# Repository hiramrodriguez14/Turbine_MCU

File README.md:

# Horizontal Axis Wind Turbine Electronic Control Unit (ECU)

## Turbine MCU PCB

Printed Circuit Board (PCB) design for the **Turbine Microcontroller Unit (MCU)** of the **Horizontal Axis Wind Turbine Electronic Control Unit (ECU)**.

This repository contains the complete KiCad hardware design, manufacturing files, and production documentation for the embedded controller responsible for turbine monitoring, blade pitch control, sensor acquisition, and communication with the Load Control & User Interface MCU.

---

# Documentation & Demo

| Resource | Link |
| ------------------------ | ------------------------------- |
| 🎥 Project Demonstration | https://www.youtube.com/watch?v=vS5Ok38P1Jk |
| 📄 Final Project Report | https://drive.google.com/file/d/1cckKhvj7mvzCEbm3IqWp0KvrUp9g6mgg/view?usp=sharing |
| 📚 Technical Appendix | https://drive.google.com/file/d/1xu7MtcffDlpna8_BUkwEc_BfjpQJpUep/view?usp=sharing |

---

# Overview

The Turbine MCU PCB serves as the dedicated embedded controller for the mechanical subsystem of the Horizontal Axis Wind Turbine Electronic Control Unit (ECU).

Designed using **KiCad**, this board interfaces directly with the turbine sensors and pitch actuation system, executing all real-time control tasks required for safe turbine operation. It operates alongside the Load Control & User Interface PCB, forming a distributed dual-MCU embedded architecture.

The PCB was designed with reliability, debugging, and manufacturability in mind, incorporating dedicated test points, modular circuitry, and production-ready manufacturing files.

---

# Engineering Highlights

- Custom 2-layer PCB
- Designed in KiCad
- Texas Instruments MSPM0G3507
- Dual servo motor interface
- Hall-effect sensor interface
- Hot-wire anemometer interface
- UART communication
- PWM generation
- Programming and debug header
- Dedicated test points
- Production-ready Gerber files
- Manufacturing BOM
- Pick-and-Place (CPL) files

---

# Hardware Features

The Turbine MCU PCB integrates the following subsystems.

### Turbine Monitoring

- Rotor RPM sensing
- Wind speed acquisition
- Sensor signal conditioning

### Pitch Control

- Dual servo motor outputs
- PWM control interface
- Blade pitch actuation

### Communication

- UART interface with the Load Control & UI MCU
- Programming and debugging interface

### System Management

- Local power regulation
- Test points
- Status indicators

---

# Hardware Architecture

The Turbine MCU PCB serves as the dedicated controller for the turbine's mechanical subsystem.

Primary responsibilities include:

- Wind speed acquisition
- Rotor speed measurement
- Blade pitch control
- Turbine state supervision
- Safety monitoring
- Communication with the Load Control & UI MCU

<p align="center">
<b>Figure 1.</b> Turbine MCU Architecture
</p>

---

# PCB Design

The PCB was developed using KiCad following standard embedded hardware design practices.

Special consideration was given to:

- Servo routing
- Sensor integrity
- Ground plane implementation
- Test point accessibility
- Programming interface accessibility
- Manufacturing compatibility

## Top Layer

<p align="center">
<b>Figure 2.</b> Top Layer PCB Layout
</p>

---

## Bottom Layer

<p align="center">
<b>Figure 3.</b> Bottom Layer PCB Layout
</p>

---

## Combined Layer View

<p align="center">
<b>Figure 4.</b> Combined PCB Layers
</p>

---

## 3D PCB View

<p align="center">
<b>Figure 5.</b> 3D PCB Rendering
</p>

---

# Manufacturing Files

This repository contains all files required for PCB fabrication and assembly.

Included manufacturing assets:

- Gerber files
- Drill files
- Pick-and-Place (CPL)
- Bill of Materials (BOM)
- Complete schematic
- PCB layout

---

# Development Tools

## PCB Design

- KiCad

## Target MCU

- Texas Instruments MSPM0G3507

---

# Repository Structure

```text
HAWT-TurbineMCU-PCB
│
├── gerbers/                   Manufacturing Gerber files
├── images/                    Documentation images
├── mylib/                     Custom KiCad component library
├── TurbineMCU.kicad_pcb       PCB layout
├── TurbineMCU.kicad_sch       Main schematic
├── TurbineMCU.kicad_pro       KiCad project
├── TurbineMCU.kicad_sym       Custom symbols
├── TurbineMCU-all-pos.csv     Pick-and-Place (CPL)
├── TurbineMCU.csv             Manufacturing BOM
├── fp-lib-table               Footprint library configuration
├── sym-lib-table              Symbol library configuration
├── README.md                  Repository documentation
└── LICENSE                    Project license
```

---

# Related Repositories

| Repository | Description |
| ------------------------ | ---------------------------------------------------------------- |
| HAWT-TurbineMCU-Firmware | Embedded firmware for turbine monitoring and blade pitch control |
| HAWT-Load_Control_and_UI | Embedded firmware for battery charging, UI, and power management |
| Load-UI_MCU              | PCB design for the Load Control & UI MCU |

---

# Authors

- Hiram R. Rodríguez Hernández
- José M. Burgos Guntín
- Sergio A. Meléndez Padilla
- Sergio A. Da Silva López

Department of Electrical & Computer Engineering

University of Puerto Rico – Mayagüez

---

# License

This project was developed for educational and research purposes as part of the Embedded Systems Design course at the University of Puerto Rico – Mayagüez.

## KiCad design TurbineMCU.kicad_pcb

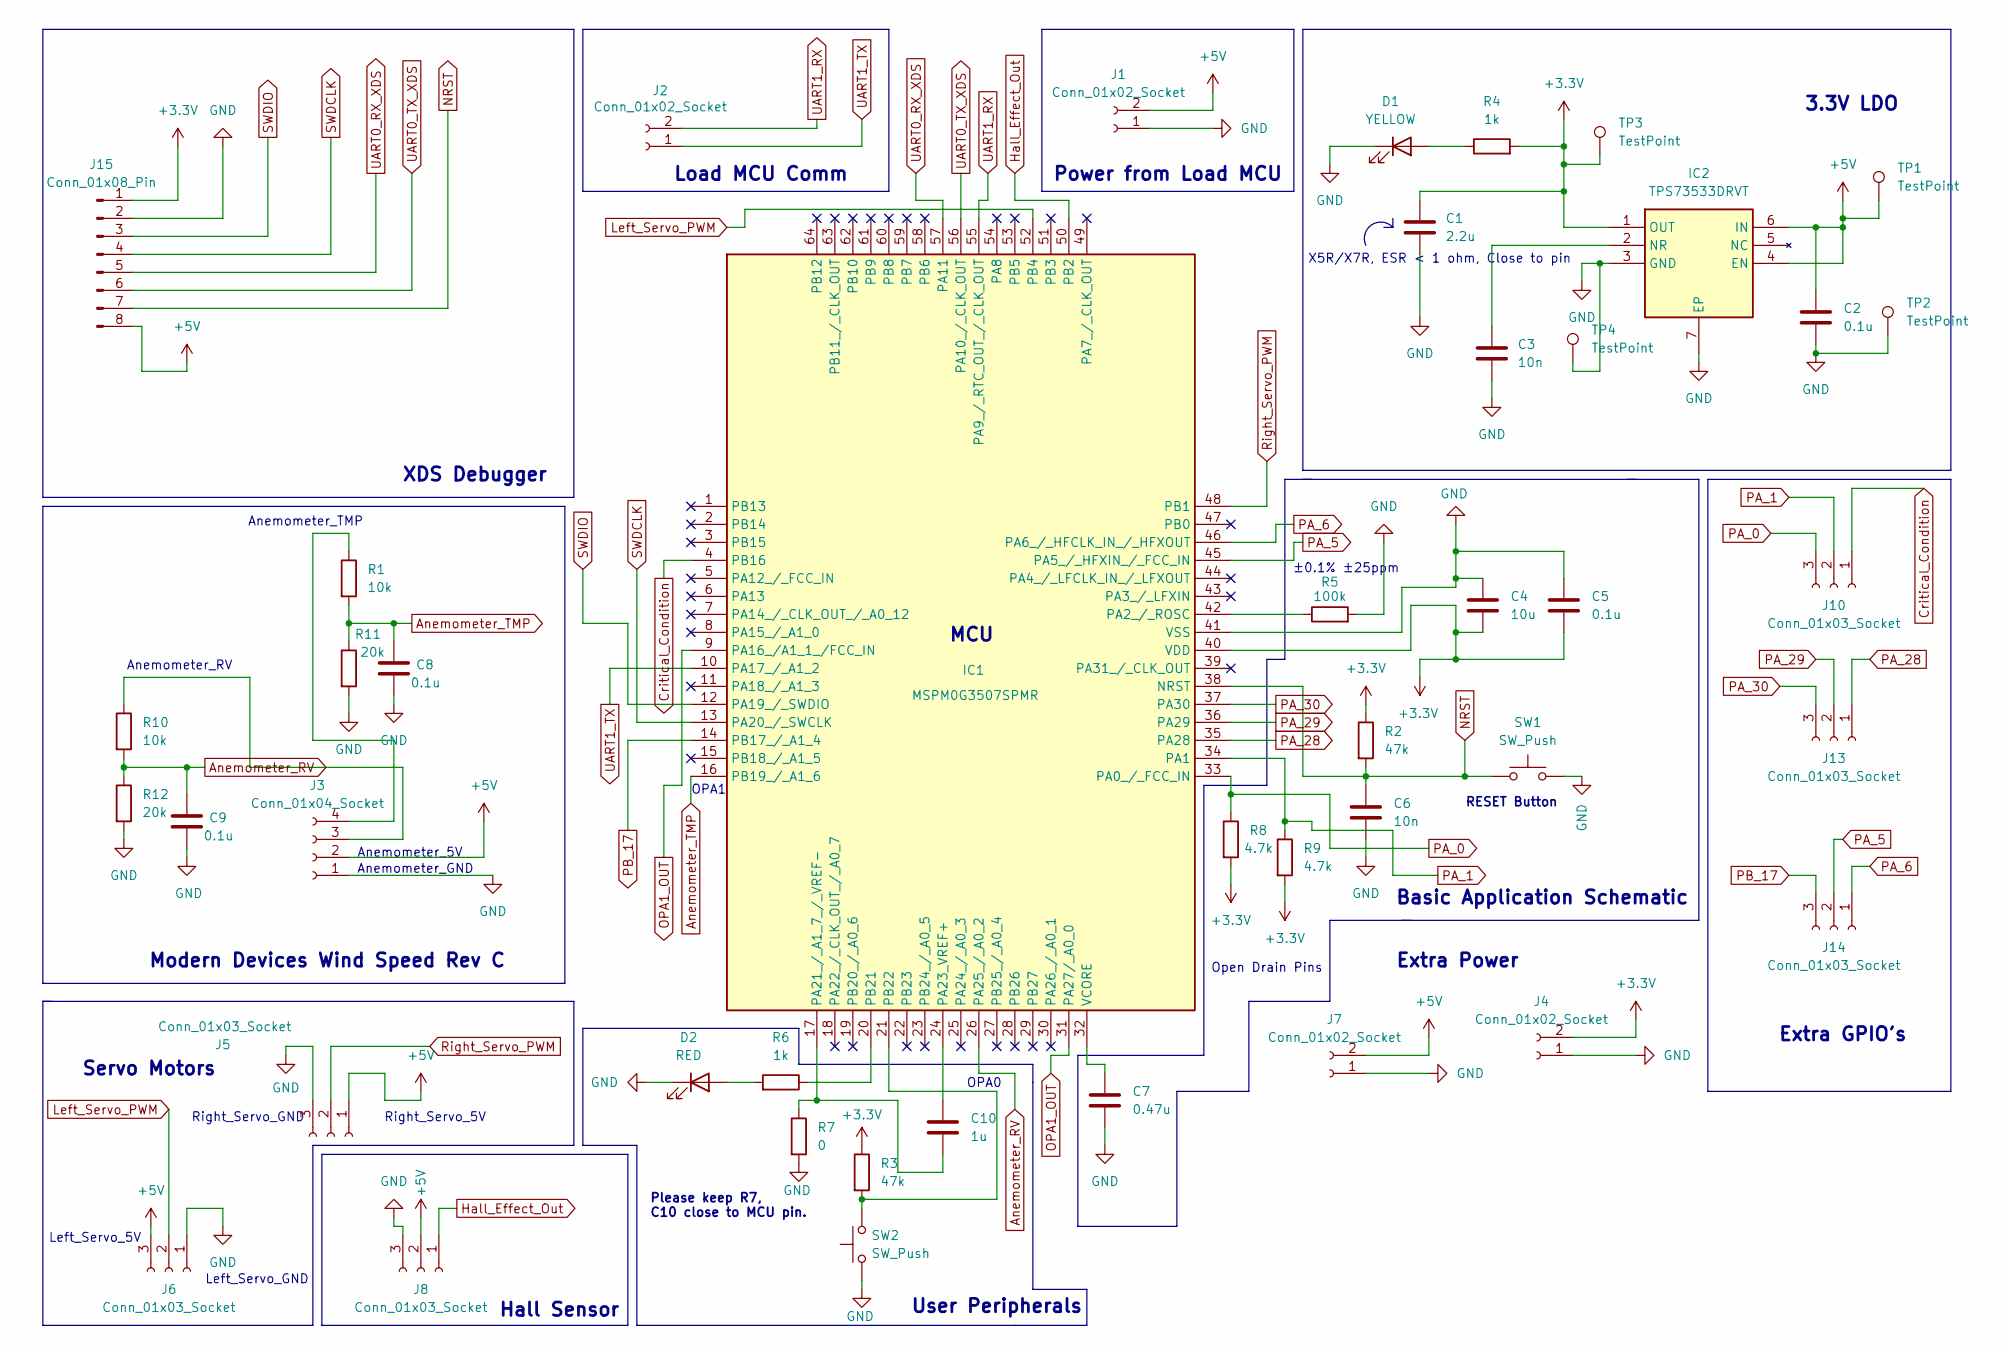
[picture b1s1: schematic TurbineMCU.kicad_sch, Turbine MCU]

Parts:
C1: 2.2u; C_1206_3216Metric_Pad1.33x1.80mm_HandSolder
C2, C5, C8, C9: 0.1u; C_0805_2012Metric_Pad1.18x1.45mm_HandSolder
C3: 10n; C_0402_1005Metric_Pad0.74x0.62mm_HandSolder
C4: 10u; C_1206_3216Metric_Pad1.33x1.80mm_HandSolder
C6: 10n; C_1206_3216Metric_Pad1.33x1.80mm_HandSolder
C7: 0.47u; C_0805_2012Metric_Pad1.18x1.45mm_HandSolder
C10: 1u; C_0402_1005Metric_Pad0.74x0.62mm_HandSolder
D1: YELLOW; LED_0805_2012Metric_Pad1.15x1.40mm_HandSolder
D2: RED; LED_0603_1608Metric_Pad1.05x0.95mm_HandSolder
IC1: MSPM0G3507SPMR; QFP50P1200X1200X160-64N; Mouser Part Number 595-MSPM0G3507SPMR
IC2: TPS73533DRVT; SON65P200X200X80-7N; Mouser Part Number 595-TPS73533DRVT
J1, J2, J4, J7: Conn_01x02_Socket; TerminalBlock_Xinya_XY308-2.54-2P_1x02_P2.54mm_Horizontal
J3: Conn_01x04_Socket; JST_XH_B4B-XH-A_1x04_P2.50mm_Vertical
J5, J6, J8: Conn_01x03_Socket; JST_XH_B3B-XH-A_1x03_P2.50mm_Vertical
J10, J13, J14: Conn_01x03_Socket; TerminalBlock_Xinya_XY308-2.54-3P_1x03_P2.54mm_Horizontal
J15: Conn_01x08_Pin; PinHeader_1x08_P2.54mm_Vertical
R1, R10: 10k; R_1206_3216Metric_Pad1.30x1.75mm_HandSolder
R2, R3: 47k; R_0805_2012Metric_Pad1.20x1.40mm_HandSolder
R4: 1k; R_0805_2012Metric_Pad1.20x1.40mm_HandSolder
R5: 100k; R_0603_1608Metric_Pad0.98x0.95mm_HandSolder
R6: 1k; R_1206_3216Metric_Pad1.30x1.75mm_HandSolder
R7: 0; R_0402_1005Metric_Pad0.72x0.64mm_HandSolder
R8, R9: 4.7k; R_0805_2012Metric_Pad1.20x1.40mm_HandSolder
R11, R12: 20k; R_1206_3216Metric_Pad1.30x1.75mm_HandSolder
SW1, SW2: SW_Push; SW_PUSH_6mm
TP1, TP2, TP3, TP4: TestPoint; TestPoint_Pad_D1.0mm

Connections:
+3.3V: C1.1, C4.2, C5.2, IC1.40 (VDD), IC2.1 (OUT), J4.2, J15.1, R2.1, R3.1, R4.2, R8.2, R9.2, TP3.1
+5V: C2.1, IC2.4 (EN), IC2.6 (IN), J1.2, J3.2, J5.1, J6.3, J7.2, J8.2, J15.8, TP1.1
Anemometer_RV: C9.1, IC1.26 (PA25_/_A0_2), R10.2, R12.1
Anemometer_TMP: C8.1, IC1.16 (PB19_/_A1_6), R1.2, R11.1
Critical_Condition: IC1.4 (PB16), J10.1
GND: C1.2, C2.2, C3.2, C4.1, C5.1, C6.2, C7.2, C8.2, C9.2, D1.1 (K), D2.1 (K), IC1.41 (VSS), IC2.3 (GND), IC2.7 (EP), J1.1, J3.1, J4.1, J5.3, J6.1, J7.1, J8.3, J15.2, R5.2, R7.2, R11.2, R12.2, SW1.2, SW2.1, TP2.1, TP4.1
Hall_Effect_Out: IC1.50 (PB2), J8.1
Left_Servo_PWM: IC1.52 (PB4), J6.2
NRST: C6.1, IC1.38 (NRST), J15.7, R2.2, SW1.1
unnamed: D1.2 (A), R4.1
unnamed: D2.2 (A), R6.2
unnamed: IC1.42 (PA2_/_ROSC), R5.1
unnamed: C10.2, IC1.17 (PA21_/_A1_7_/_VREF-), R7.1
unnamed: C10.1, IC1.24 (PA23_VREF+)
unnamed: IC1.20 (PB21), R6.1
unnamed: IC1.21 (PB22), R3.2, SW2.2
unnamed: C7.1, IC1.32 (VCORE)
unnamed: C3.1, IC2.2 (NR)
unnamed: J3.3, R10.1
unnamed: J3.4, R1.1
OPA1_OUT: IC1.9 (PA16_/A1_1_/FCC_IN), IC1.31 (PA27/_A0_0)
PA_0: IC1.33 (PA0_/_FCC_IN), J10.3, R8.1
PA_1: IC1.34 (PA1), J10.2, R9.1
PA_5: IC1.45 (PA5_/_HFXIN_/_FCC_IN), J14.2
PA_6: IC1.46 (PA6_/_HFCLK_IN_/_HFXOUT), J14.1
PA_28: IC1.35 (PA28), J13.1
PA_29: IC1.36 (PA29), J13.2
PA_30: IC1.37 (PA30), J13.3
PB_17: IC1.14 (PB17_/_A1_4), J14.3
Right_Servo_PWM: IC1.48 (PB1), J5.2
SWDCLK: IC1.13 (PA20_/_SWCLK), J15.4
SWDIO: IC1.12 (PA19_/_SWDIO), J15.3
UART0_RX_XDS: IC1.57 (PA11), J15.5
UART0_TX_XDS: IC1.56 (PA10_/_CLK_OUT), J15.6
UART1_RX: IC1.55 (PA9_/_RTC_OUT_/_CLK_OUT), J2.2
UART1_TX: IC1.10 (PA17_/_A1_2), J2.1

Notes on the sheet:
User Peripherals
Hall Sensor
Basic Application Schematic
OPA0
Left_Servo_GND
Left_Servo_5V
Anemometer_5V
Please keep R7, C10 close to MCU pin.
Load MCU Comm
OPA1
Right_Servo_5V
RESET Button
Anemometer_TMP
X5R/X7R, ESR < 1 ohm, Close to pin
Open Drain Pins
3.3V LDO
Right_Servo_GND
Extra GPIO's
±0.1% ±25ppm
Modern Devices Wind Speed Rev C
Extra Power
Servo Motors
Anemometer_RV
XDS Debugger
MCU
Anemometer_GND
Power from Load MCU

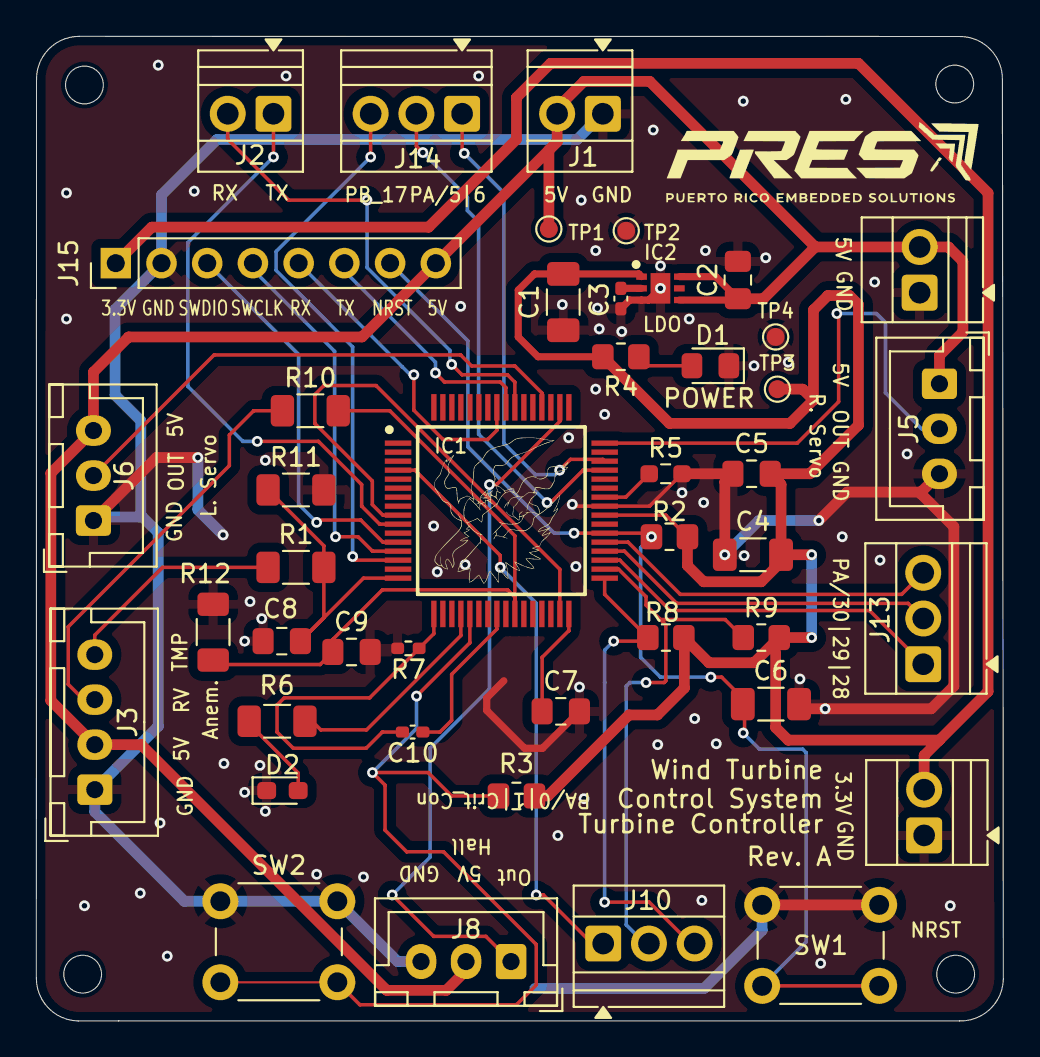
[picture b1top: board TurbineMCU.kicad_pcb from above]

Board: 2 copper layers, 53.7 x 54.7 mm, 44 parts (0 on the bottom side), 36 nets.

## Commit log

2026-04-30 Initial KiCad project commit
2026-04-30 Rename project from Load-UI_MCU to Turbine Controller
2026-04-30 Fixed library and step model path
2026-04-30 Fixed IC2 silkscreen
2026-04-30 silkscreen
2026-05-01 Improved LDO layout based on manufacturer guidelines
2026-05-01 pick and place file added
2026-05-01 final layout
2026-05-01 board finished
2026-05-05 Added testpoints
2026-05-20 ready for manufacturing
2026-05-21 This commit contains all files up dotae to Rev A. Turbine MCU, manufactured on May 21, 2026
2026-06-20 Fixed silks screen
2026-06-21 Add new file dudu.c with initial content
2026-06-21 Update figure caption from 'Turbine MCU Hardware' to 'System'
2026-06-21 Update architecture image and caption in README
2026-06-21 Update repository name in README
